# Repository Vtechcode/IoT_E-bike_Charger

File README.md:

# IoT Enable E-bike Charger Integrating Remote Monitoring and Billing

Electric bikes (e-bikes) are rapidly gaining traction worldwide, including in Kenya.
In Kenya, adoption is rising, particularly among urban and peri-urban commuters who view e-bikes as a cost-effective and sustainable transport option.
A major challenge remains the limited access to affordable and readily available charging infrastructure. Most charging systems are imported, expensive, and not optimized for small-scale operators such as boda boda riders and last-mile delivery services.
There is a need for low-cost, locally adaptable charging solutions with smart monitoring and billing features tailored to the Kenyan e-bike ecosystem.

## 🛠️ Technologies Used
Microcontroller: RaspberryPi Pico / ESP32 <br>
Language: C / C++ / Java / Python <br>
IDE: Thonny IDE / Arduino IDE / Android Studio <br>

## ⚙️ Features
1 52V 8A output <br>
2 Can charge a 13Ah battery within 1.6 hrs <br>
3 Remote Control of the charger ie User can switch on and off the charger remotely <br>
4 Remote monitoring of the power output -> the charger has a current sensor that measures the current, the readings are sent to Firebase via wifi <br>
5 Automatic billing -> the billing is done based on energy consumed in real time and the user can see the amout via our mobile app <br>
6 User friendly mobile app <br>

## 📸 Final Charger

## 📸 Charger Testing

## 📸 Control PCB

## 📸 Rectification PCB

## 📸 Control Schematic

## 📸 Rectification Schematic

## 📸 Firebase Database

## 📸 Android App

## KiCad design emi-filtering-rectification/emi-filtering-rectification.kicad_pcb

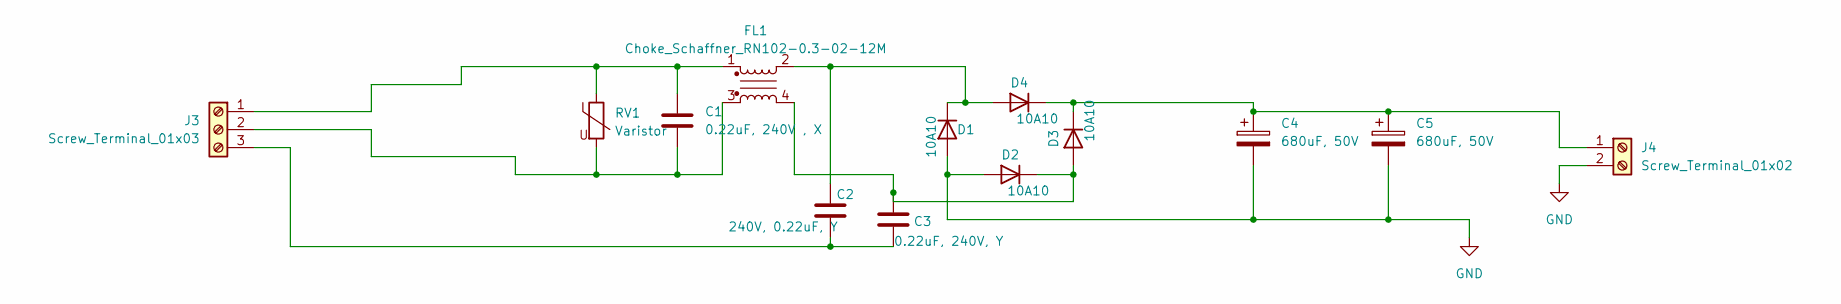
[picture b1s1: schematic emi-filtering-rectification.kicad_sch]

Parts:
C1: 0.22uF, 240V , X; CAPRR1500W80L1800T500H1050
C2: 240V, 0.22uF, Y; C_Disc_D4.7mm_W2.5mm_P5.00mm
C3: 0.22uF, 240V, Y; C_Disc_D4.7mm_W2.5mm_P5.00mm
C4, C5: 680uF, 50V; CP_Radial_D10.0mm_P7.50mm
D1, D2, D3, D4: 10A10; D_DO-201AD_P15.24mm_Horizontal
FL1: Choke_Schaffner_RN102-0.3-02-12M; COMMON MODE CHOKE
J3: Screw_Terminal_01x03; TerminalBlock_Phoenix_MKDS-1,5-3-5.08_1x03_P5.08mm_Horizont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
J4: Screw_Terminal_01x02; TerminalBlock_Phoenix_MKDS-1,5-2-5.08_1x02_P5.08mm_Horizont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
RV1: Varistor; RV_Disc_D21.5mm_W4.3mm_P10mm

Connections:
GND: C4.2, C5.2, D1.2 (A), D2.2 (A), J4.2
unnamed: C2.1, D1.1 (K), D4.2 (A), FL1.2
unnamed: C3.1, D2.1 (K), D3.2 (A), FL1.4
unnamed: C4.1, C5.1, D3.1 (K), D4.1 (K), J4.1
unnamed: C1.1, FL1.1, J3.1, RV1.1
unnamed: C1.2, FL1.3, J3.2, RV1.2
unnamed: C2.2, C3.2, J3.3

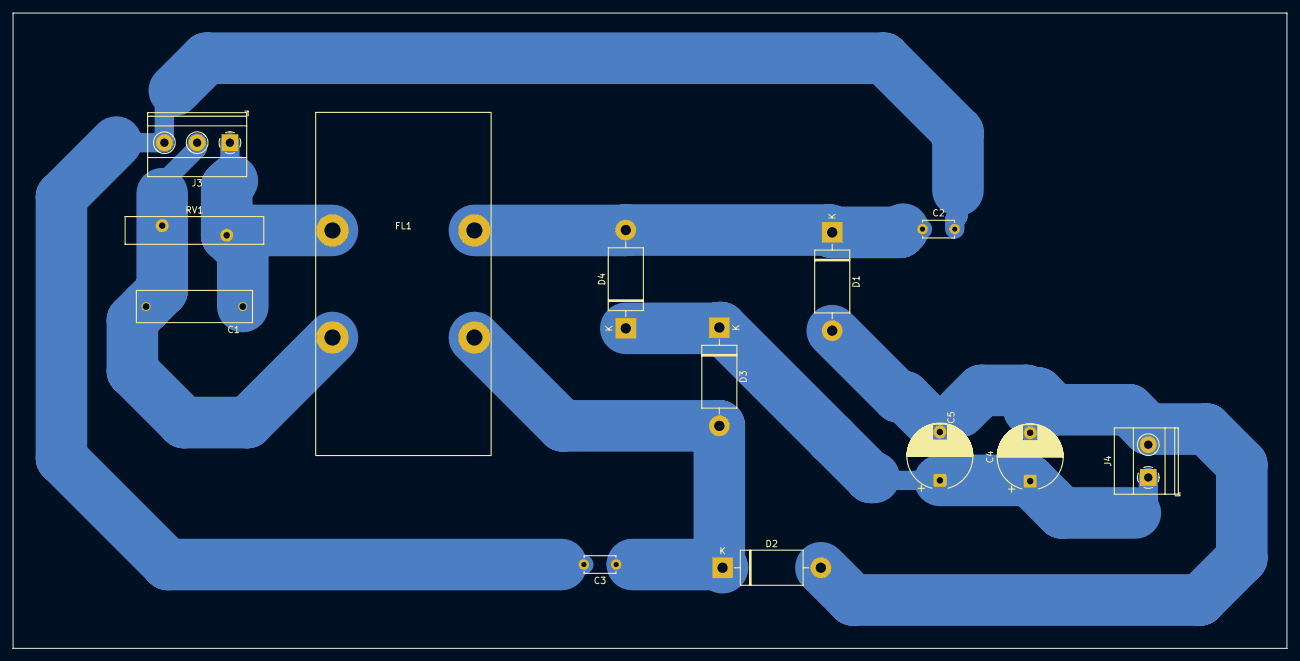
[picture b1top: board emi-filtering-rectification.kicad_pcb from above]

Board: 2 copper layers, 197.5 x 98.5 mm, 13 parts (0 on the bottom side), 7 nets.

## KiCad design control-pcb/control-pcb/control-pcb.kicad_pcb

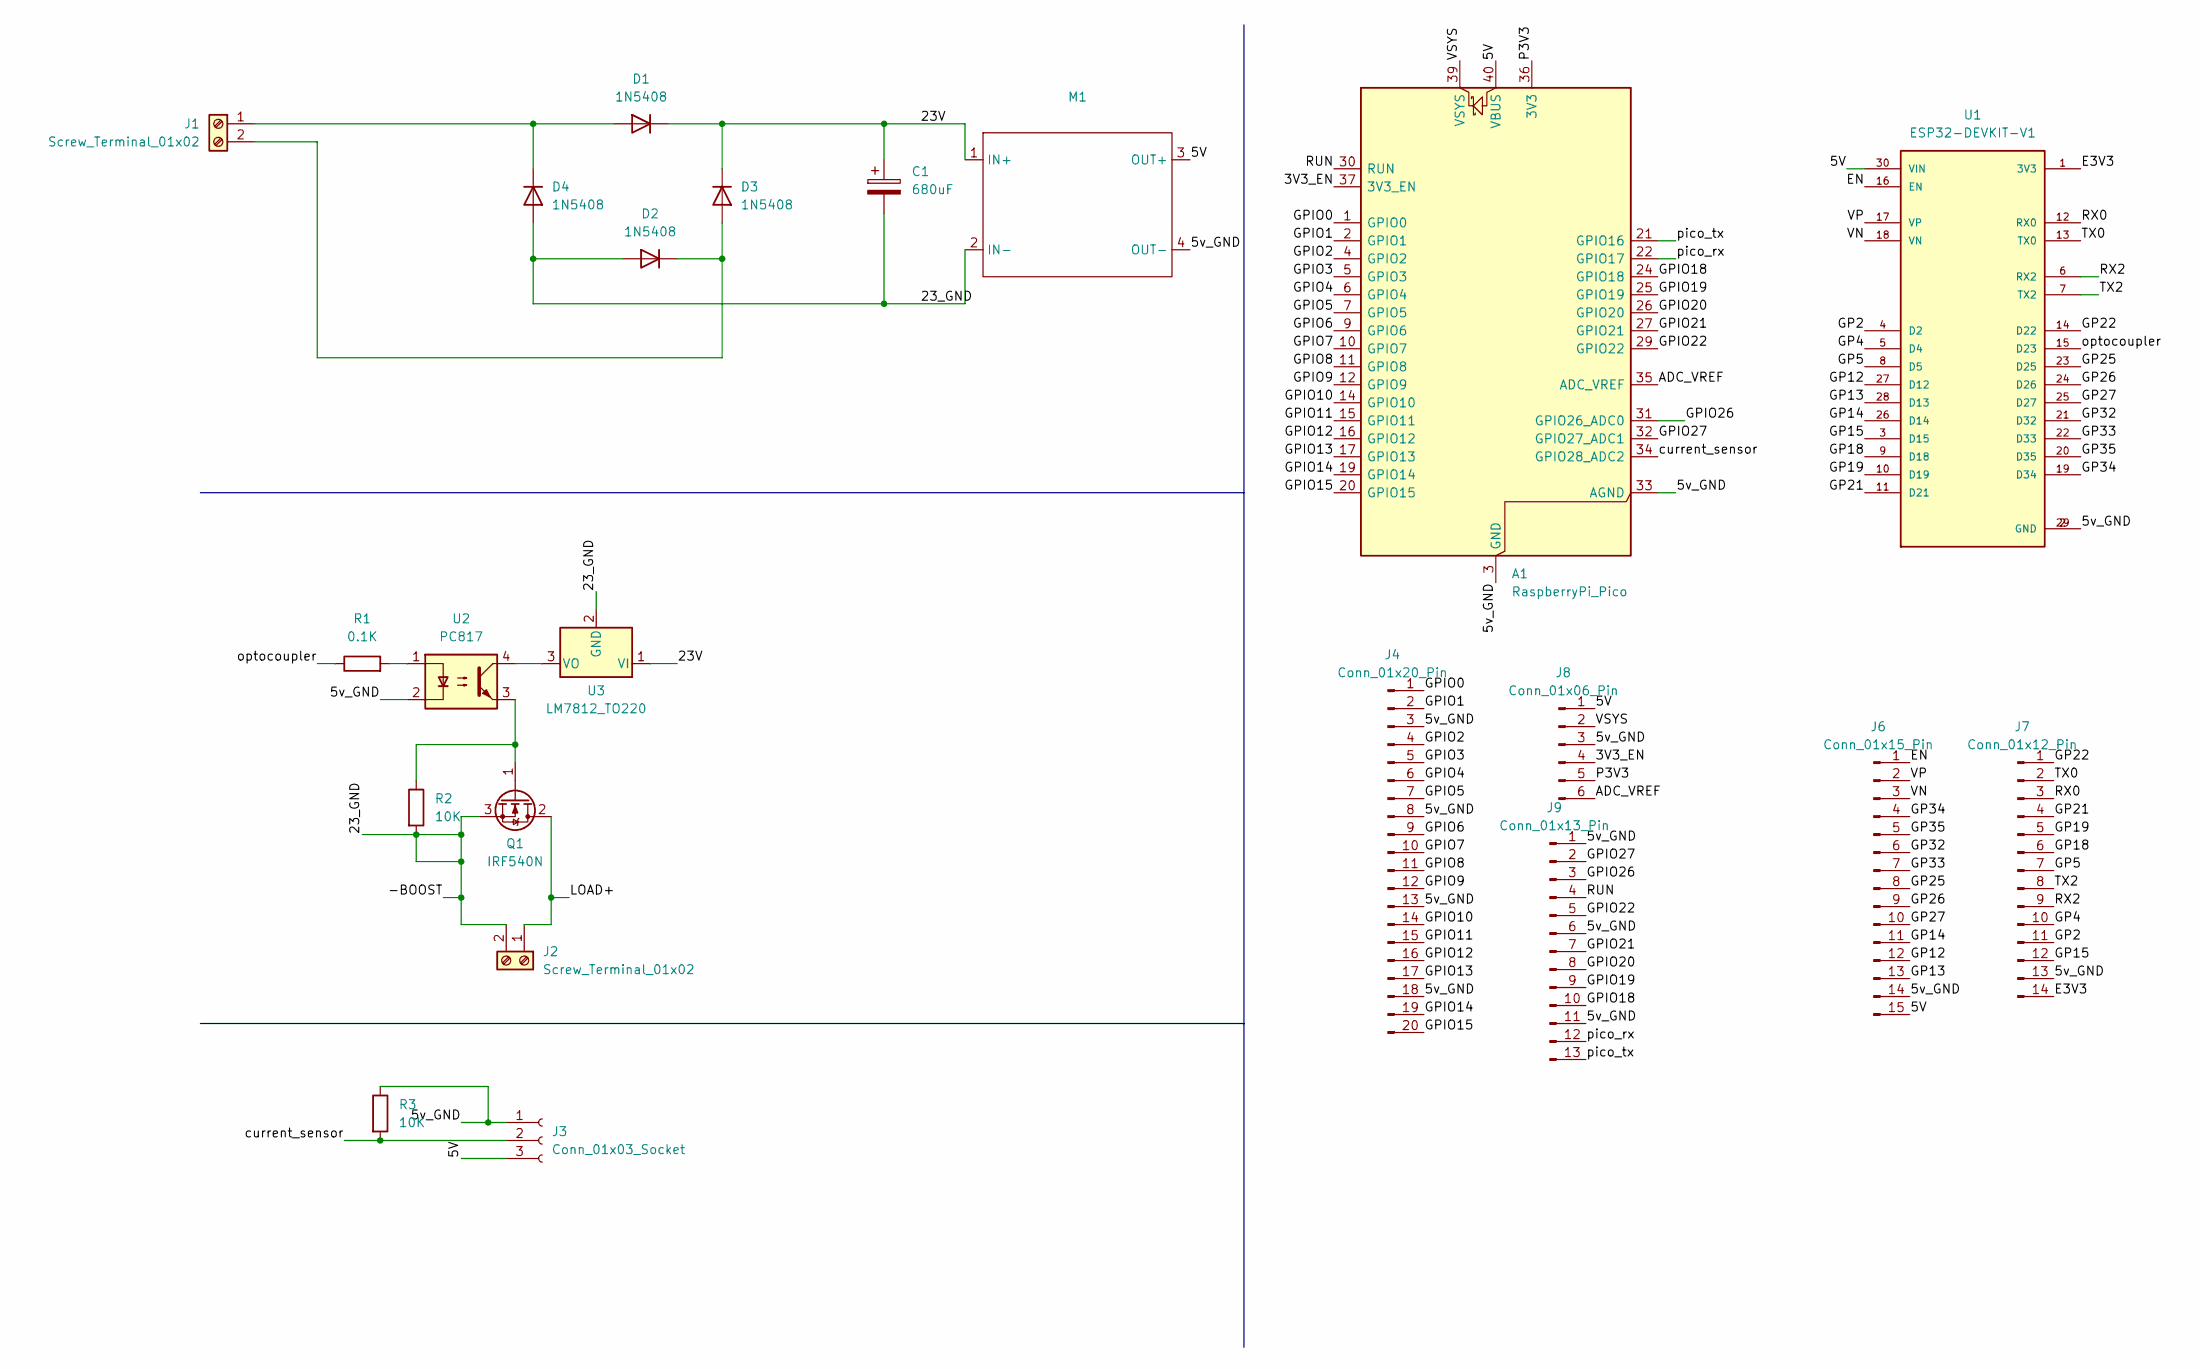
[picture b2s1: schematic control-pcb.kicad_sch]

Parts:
A1: RaspberryPi_Pico; RaspberryPi_Pico_Common_Unspecified
C1: 680uF; CP_Radial_D18.0mm_P7.50mm
D1, D2, D3, D4: 1N5408; D_DO-201AD_P15.24mm_Horizontal
J1, J2: Screw_Terminal_01x02; TerminalBlock_Phoenix_MKDS-1,5-2-5.08_1x02_P5.08mm_Horizont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
J3: Conn_01x03_Socket; PinSocket_1x03_P2.54mm_Vertical
J4: Conn_01x20_Pin; PinHeader_1x20_P2.54mm_Vertical
J6: Conn_01x15_Pin; PinHeader_1x15_P2.54mm_Vertical
J7: Conn_01x12_Pin; PinHeader_1x14_P2.54mm_Vertical
J8: Conn_01x06_Pin; PinHeader_1x06_P2.54mm_Vertical
J9: Conn_01x13_Pin; PinHeader_1x13_P2.54mm_Vertical
M1: buck-converter-module
Q1: IRF540N; TO-220-3_Vertical
R1: 0.1K; R_Axial_DIN0414_L11.9mm_D4.5mm_P15.24mm_Horizontal
R2, R3: 10K; R_Axial_DIN0411_L9.9mm_D3.6mm_P15.24mm_Horizontal
U1: ESP32-DEVKIT-V1; MODULE_ESP32_DEVKIT_V1; PARTREV N/A
U2: PC817; DIP-4_W7.62mm
U3: LM7812_TO220; TO-220-3_Vertical

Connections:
/3V3_EN: A1.37 (3V3_EN), J8.4
/5V: A1.40 (VBUS), J3.3, J6.15, J8.1, M1.3 (OUT+), U1.30 (VIN)
/5v_GND: A1.3 (GND), A1.8 (GND), A1.13 (GND), A1.18 (GND), A1.23 (GND), A1.28 (GND), A1.33 (AGND), A1.38 (GND), J3.1, J4.3, J4.8, J4.13, J4.18, J6.14, J7.13, J8.3, J9.1, J9.6, J9.11, M1.4 (OUT-), R3.1, U1.2 (GND), U1.29 (GND), U2.2
/23V: C1.1, D1.1 (K), D3.1 (K), M1.1 (IN+), U3.1 (VI)
/-BOOST: C1.2, D2.2 (A), D4.2 (A), J2.2, M1.2 (IN-), Q1.3 (S), R2.2, U3.2 (GND)
/ADC_VREF: A1.35 (ADC_VREF), J8.6
/E3V3: J7.14, U1.1 (3V3)
/EN: J6.1, U1.16 (EN)
/GP2: J7.11, U1.4 (D2)
/GP4: J7.10, U1.5 (D4)
/GP5: J7.7, U1.8 (D5)
/GP12: J6.12, U1.27 (D12)
/GP13: J6.13, U1.28 (D13)
/GP14: J6.11, U1.26 (D14)
/GP15: J7.12, U1.3 (D15)
/GP18: J7.6, U1.9 (D18)
/GP19: J7.5, U1.10 (D19)
/GP21: J7.4, U1.11 (D21)
/GP22: J7.1, U1.14 (D22)
/GP25: J6.8, U1.23 (D25)
/GP26: J6.9, U1.24 (D26)
/GP27: J6.10, U1.25 (D27)
/GP32: J6.6, U1.21 (D32)
/GP33: J6.7, U1.22 (D33)
/GP34: J6.4, U1.19 (D34)
/GP35: J6.5, U1.20 (D35)
/GPIO0: A1.1 (GPIO0), J4.1
/GPIO1: A1.2 (GPIO1), J4.2
/GPIO2: A1.4 (GPIO2), J4.4
/GPIO3: A1.5 (GPIO3), J4.5
/GPIO4: A1.6 (GPIO4), J4.6
/GPIO5: A1.7 (GPIO5), J4.7
/GPIO6: A1.9 (GPIO6), J4.9
/GPIO7: A1.10 (GPIO7), J4.10
/GPIO8: A1.11 (GPIO8), J4.11
/GPIO9: A1.12 (GPIO9), J4.12
/GPIO10: A1.14 (GPIO10), J4.14
/GPIO11: A1.15 (GPIO11), J4.15
/GPIO12: A1.16 (GPIO12), J4.16
/GPIO13: A1.17 (GPIO13), J4.17
/GPIO14: A1.19 (GPIO14), J4.19
/GPIO15: A1.20 (GPIO15), J4.20
/GPIO18: A1.24 (GPIO18), J9.10
/GPIO19: A1.25 (GPIO19), J9.9
/GPIO20: A1.26 (GPIO20), J9.8
/GPIO21: A1.27 (GPIO21), J9.7
/GPIO22: A1.29 (GPIO22), J9.5
/GPIO26: A1.31 (GPIO26_ADC0), J9.3
/GPIO27: A1.32 (GPIO27_ADC1), J9.2
/LOAD+: J2.1, Q1.2 (D)
/P3V3: A1.36 (3V3), J8.5
/RUN: A1.30 (RUN), J9.4
/RX0: J7.3, U1.12 (RX0)
/RX2: J7.9, U1.6 (RX2)
/TX0: J7.2, U1.13 (TX0)
/TX2: J7.8, U1.7 (TX2)
/VN: J6.3, U1.18 (VN)
/VP: J6.2, U1.17 (VP)
/VSYS: A1.39 (VSYS), J8.2
/current_sensor: A1.34 (GPIO28_ADC2), J3.2, R3.2
/optocoupler: R1.1, U1.15 (D23)
/pico_rx: A1.22 (GPIO17), J9.12
/pico_tx: A1.21 (GPIO16), J9.13
unnamed: D1.2 (A), D4.1 (K), J1.1
unnamed: D2.1 (K), D3.2 (A), J1.2
unnamed: Q1.1 (G), R2.1, U2.3
unnamed: R1.2, U2.1
unnamed: U2.4, U3.3 (VO)

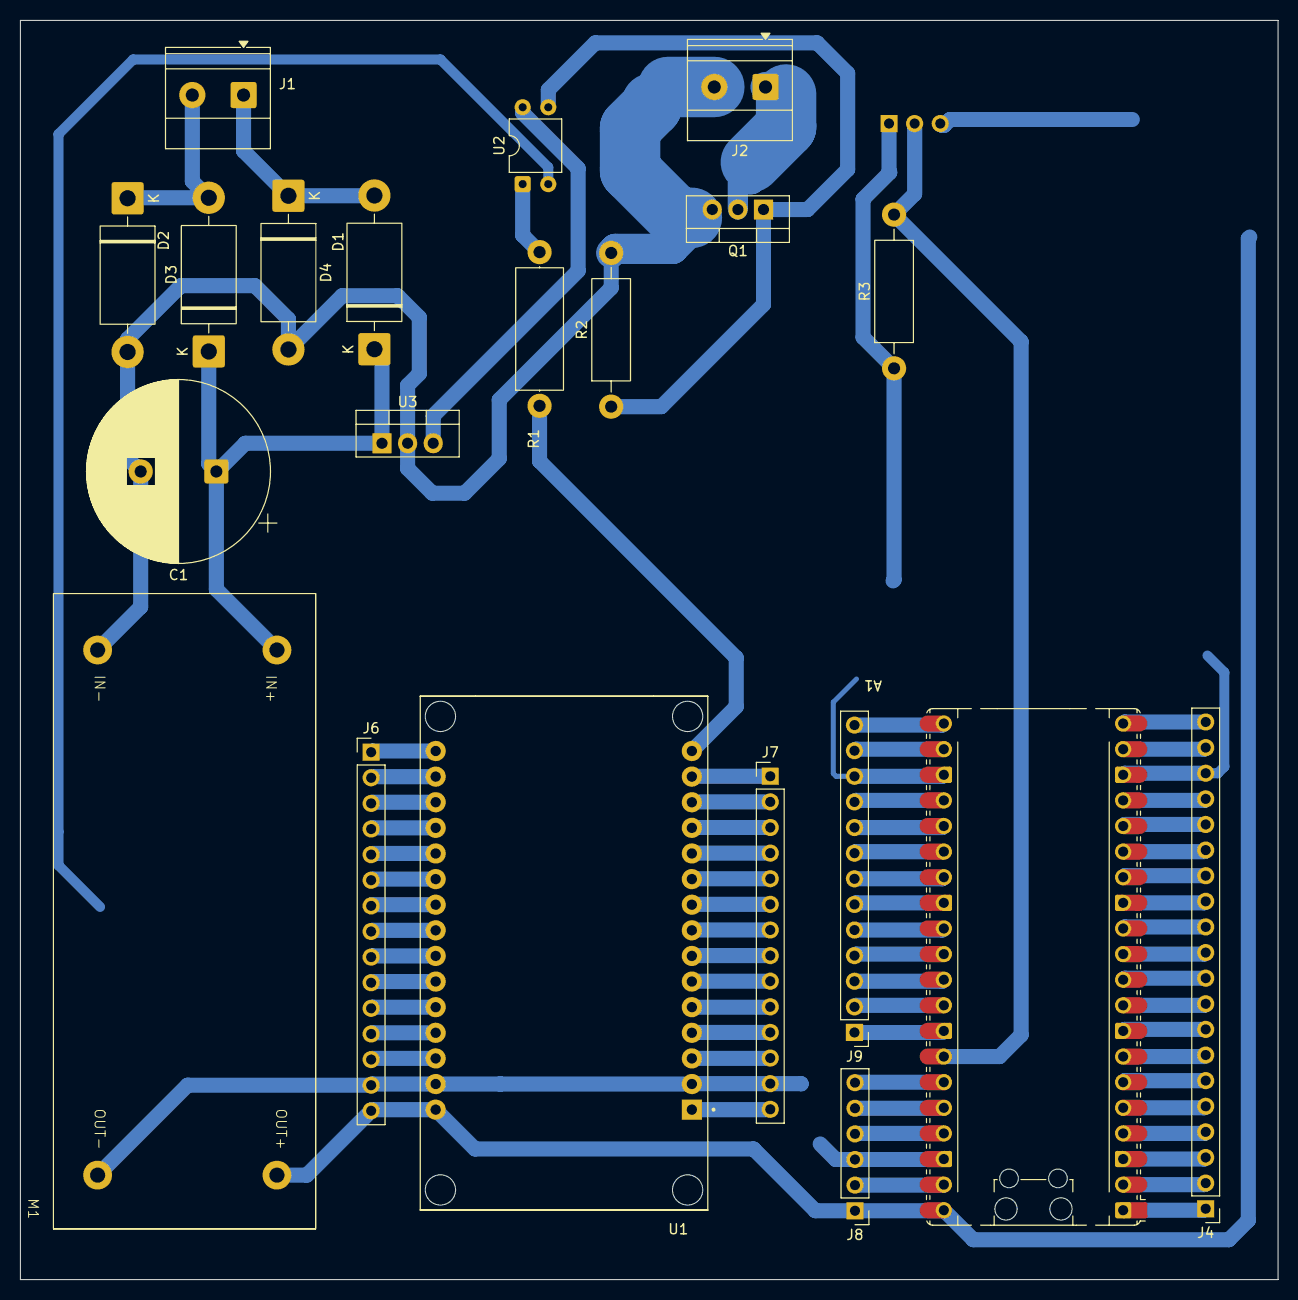
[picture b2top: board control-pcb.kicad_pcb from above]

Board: 2 copper layers, 124.7 x 124.8 mm, 22 parts (1 on the bottom side), 68 nets.

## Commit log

2026-02-24 Final Version
2026-02-24 Modified schematic
2026-02-27 Added more images
2026-02-28 added image
